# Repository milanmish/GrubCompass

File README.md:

# Grub Compass

I'm building a compass that will point me and my friends to a random restaurant nearby.

We always have trouble deciding on a place to eat, so I'm building a device that does the job for us. After randomly picking a restaurant within a certain radius from our location, the compass needle will point in the direction of the unknown location. We then need to follow the compass until we reach the restaurant.

**Hardware:**
-  ESP32-DevKitC ([Datasheet](https://mm.digikey.com/Volume0/opasdata/d220001/medias/docus/754/ESP32-DevKitC_GSG_Ver1.4_2017.pdf))
- Adafruit PA1010D GPS ([Datasheet](https://cdn-learn.adafruit.com/downloads/pdf/adafruit-mini-gps-pa1010d-module.pdf))
- Adafruit LIS3MDL Magnetometer ([Datasheet](https://mm.digikey.com/Volume0/opasdata/d220001/medias/docus/60/4479_Web.pdf))
- Continuous servo motor

**Useful Resources:**
- [LIS3MDL Github Repo](https://github.com/adafruit/Adafruit_LIS3MDL/tree/master)
- [PA1010D Github Repo](https://github.com/adafruit/Adafruit_GPS)
- [Magnetic field strength to compass heading conversion](https://aerospace.honeywell.com/content/dam/aerobt/en/documents/learn/products/sensors/application-notes/AN203_Compass_Heading_Using_Magnetometers.pdf)

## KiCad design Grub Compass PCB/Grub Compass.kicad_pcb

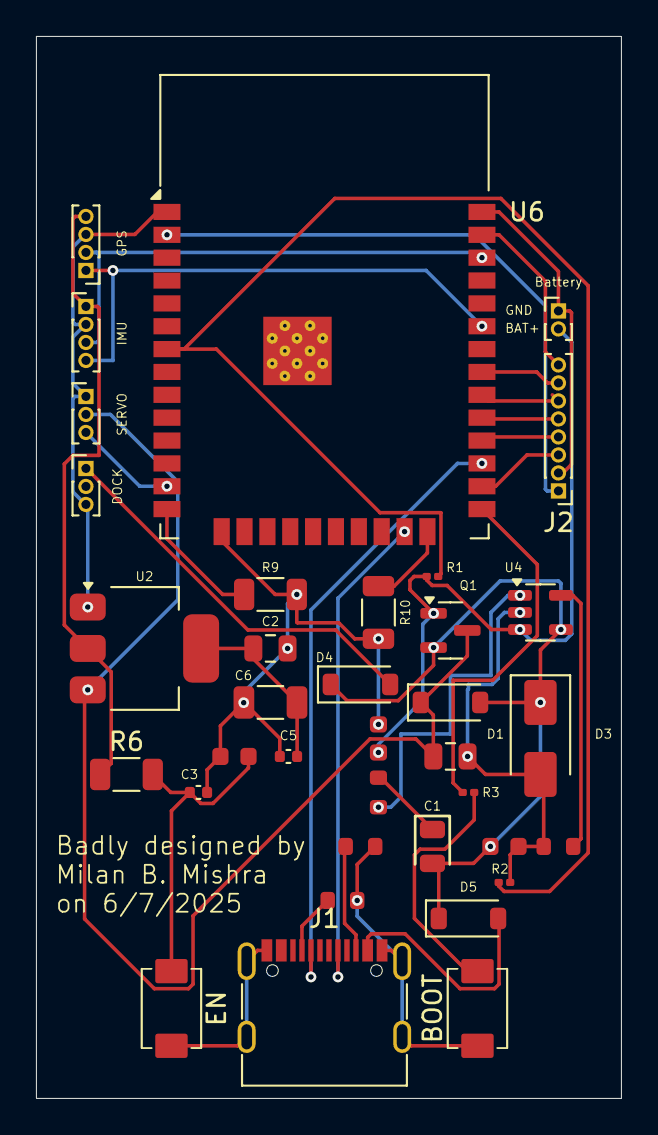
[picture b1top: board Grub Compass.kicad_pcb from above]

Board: 2 copper layers, 32.5 x 59.0 mm, 36 parts (0 on the bottom side), 30 nets.

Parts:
BOOT: TS-1088-AR02016
Battery: Conn_01x02_Pin; PinHeader_1x02_P1.00mm_Vertical
C1: 10uF; C_0805_2012Metric
C2: 22uF; C_0805_2012Metric
C3, C5: 100nF; C_0402_1005Metric
C4: 1uF; C_0603
C6: 22uF; C_1206_3216Metric
C7, C8: 4.7uF; C_0603
D1: 1N4148W; D_SOD-123
D2: Green; D_0805
D3: SMAJ5.0A; D_SMA
D4, D5: 1N5819; D_SOD-123
DOCK: Conn_01x03_Pin; PinHeader_1x03_P1.00mm_Vertical
EN: TS-1088-AR02016
GPS: Conn_01x04_Pin; PinHeader_1x04_P1.00mm_Vertical
IMU: Conn_01x04_Pin; PinHeader_1x04_P1.00mm_Vertical
J1: USB_C_Receptacle_USB2.0_16P; USB_C_Receptacle_G-Switch_GT-USB-7010ASV
J2: Conn_01x08_Pin; PinHeader_1x08_P1.00mm_Vertical
Q1: IRLML6302TRPBF; SOT-23
R1, R2: 100K; R_0201_0603Metric
R3: 100R; R_0201_0603Metric
R4, R5: 5.1k; R_0603
R6, R9, R10: 10K; R_1206_3216Metric
R7: 2k; R_0603
R8: 470R; R_0603
SERVO: Conn_01x03_Pin; PinHeader_1x03_P1.00mm_Vertical
U2: AMS1117-3.3; SOT-223-3_TabPin2
U4: MCP73831-2-OT; SOT-23-5
U6: ESP32-WROOM-32E; ESP32-WROOM-32D

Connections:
+3.3V: C2.1, C5.2, C6.2, GPS.4, IMU.1, R6.1, U2.2 (VO)
+3V3: J2.1, U6.2 (VDD)
BAT+: Battery.2 (BAT+), C7.1, Q1.1 (D), R1.1, U4.3 (V_{BAT})
BAT_MEAS: R1.2, R2.1, U6.7 (IO35)
BOOT: R3.1, U6.25 (IO0)
EN: C3.1, C4.2, EN.1 (A), R6.2, U6.3 (EN)
GND: BOOT.2 (B), Battery.1 (GND), C1.2, C2.2, C3.2, C4.1, C5.1, C6.1, C7.2, C8.2, D3.2 (A2), DOCK.3, EN.2 (B), GPS.3, IMU.2, J1.A1 (GND), J1.A12 (GND), J1.B1 (GND), J1.B12 (GND), J1.S1 (SHIELD), J2.2, R2.2, R4.2, R5.2, R7.1, R9.2, R10.2, SERVO.1, U2.1 (GND), U4.2 (V_{SS}), U6.1 (GND), U6.15 (GND), U6.38 (GND), U6.39 (GND)
unnamed: D4.2 (A), DOCK.1
unnamed: D2.1, R8.1
unnamed: D5.2 (A), J1.A4 (VBUS), J1.A9 (VBUS), J1.B4 (VBUS), J1.B9 (VBUS)
unnamed: J1.A5 (CC1), R4.1
unnamed: J1.B5 (CC2), R5.1
unnamed: J2.3, U6.26 (IO4)
unnamed: J2.4, U6.28 (IO17)
unnamed: J2.5, U6.29 (IO5)
unnamed: J2.6, U6.30 (IO18)
unnamed: J2.7, U6.31 (IO19)
unnamed: J2.8, U6.37 (IO23)
unnamed: BOOT.1 (A), R3.2
unnamed: R7.2, U4.5 (PROG)
unnamed: R8.2, U4.1 (STAT)
unnamed: R10.1, U6.24 (IO2)
unnamed: R9.1, U6.14 (IO12)
SCL: GPS.2, IMU.3, U6.36 (IO22)
SDA: GPS.1, IMU.4, U6.33 (IO21)
SERVO_5V: C1.1, D1.1 (K), Q1.3 (S), SERVO.2, U2.3 (VI)
SERVO_PWM: SERVO.3, U6.13 (IO14)
USB_5V: C8.1, D1.2 (A), D2.2, D3.1 (A1), D4.1 (K), D5.1 (K), Q1.2 (G), U4.4 (V_{DD})
USB_D+: J1.A6 (D+), J1.B6 (D+), U6.23 (IO15)
USB_D-: J1.A7 (D-), J1.B7 (D-), U6.27 (IO16)

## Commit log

2025-05-22 Journal update
2025-05-26 PCB Files
2025-05-26 Img changes
2025-05-28 Day 3 update
2025-05-30 Day 4ish
2025-06-07 PCB Day 3
2025-06-07 Breaking more things
2025-07-28 Create git repo
2025-07-28 Quick Update
